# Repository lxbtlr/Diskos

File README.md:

# Diskos
Working directory for all Project Diskos materials

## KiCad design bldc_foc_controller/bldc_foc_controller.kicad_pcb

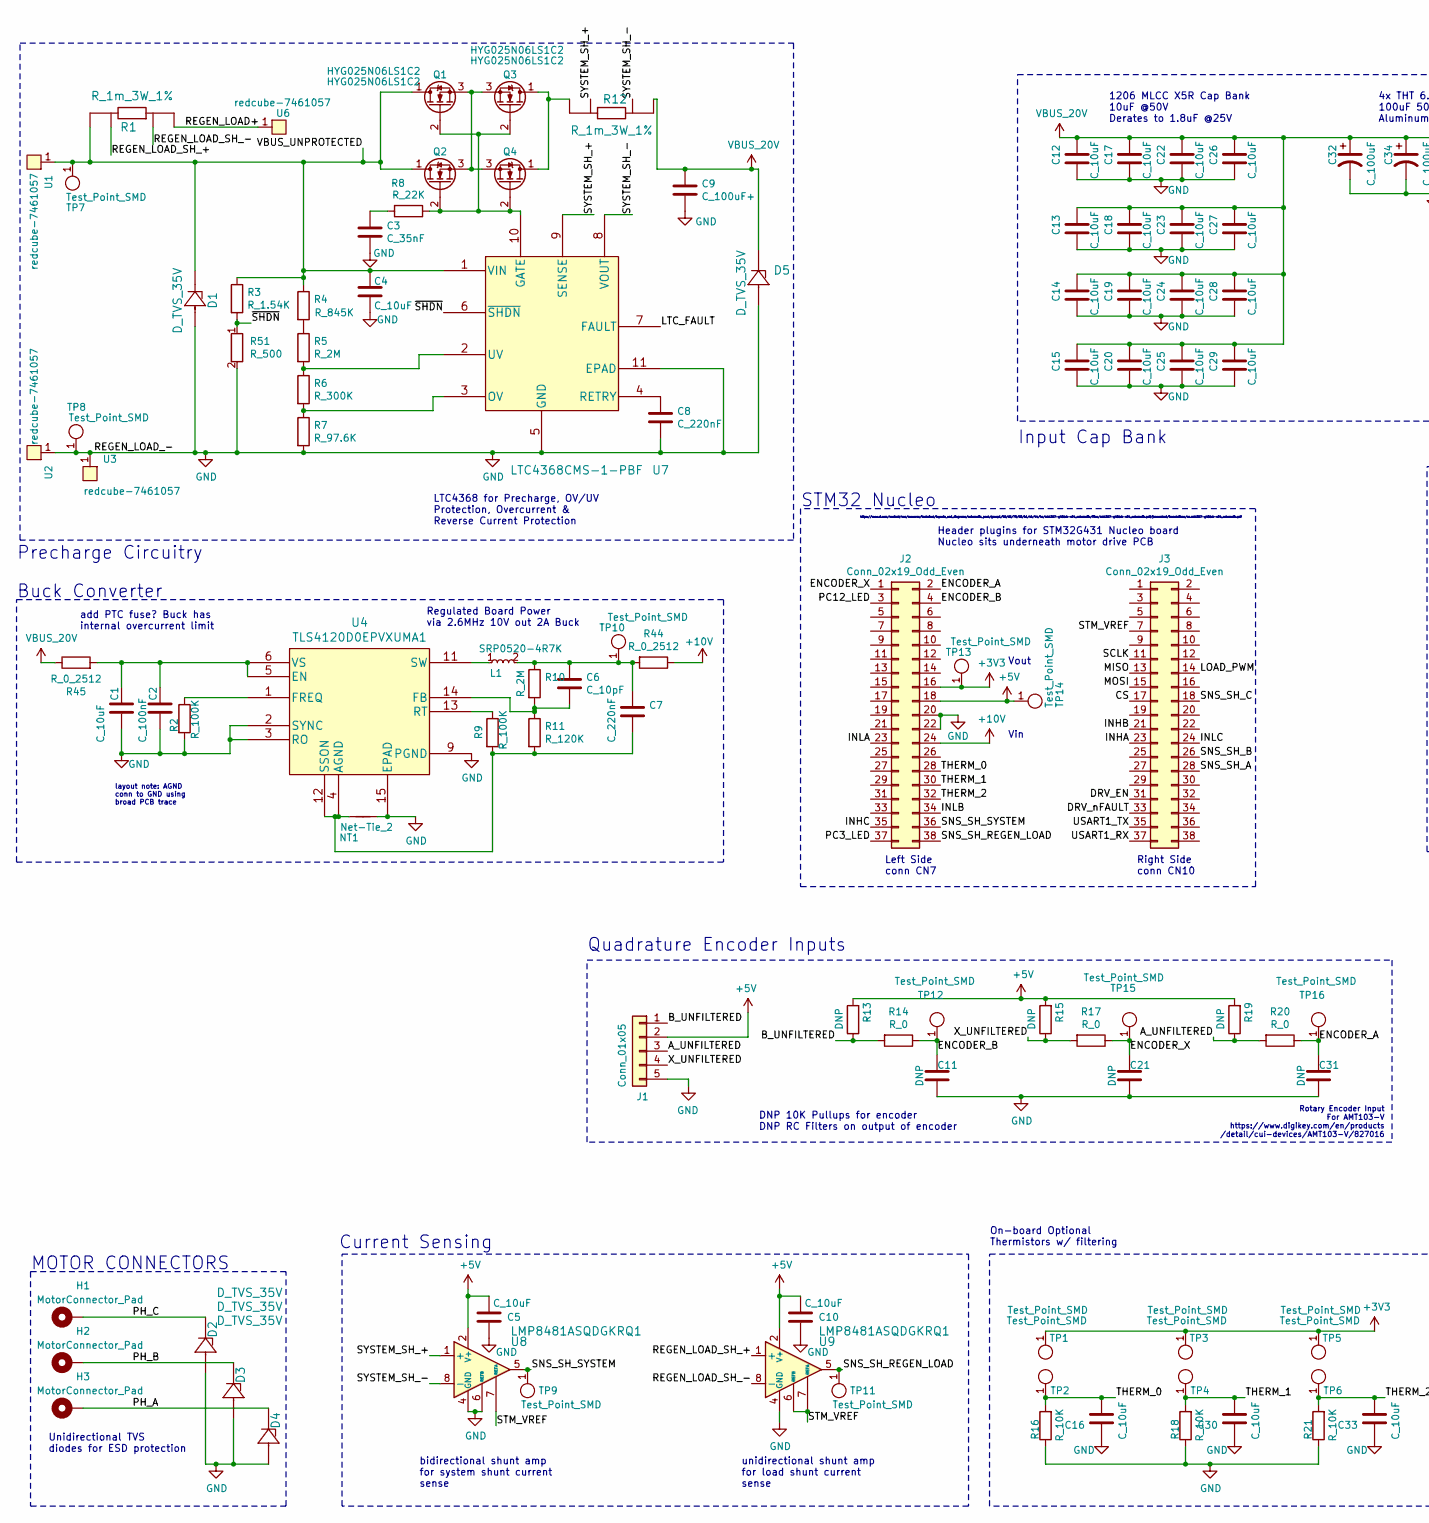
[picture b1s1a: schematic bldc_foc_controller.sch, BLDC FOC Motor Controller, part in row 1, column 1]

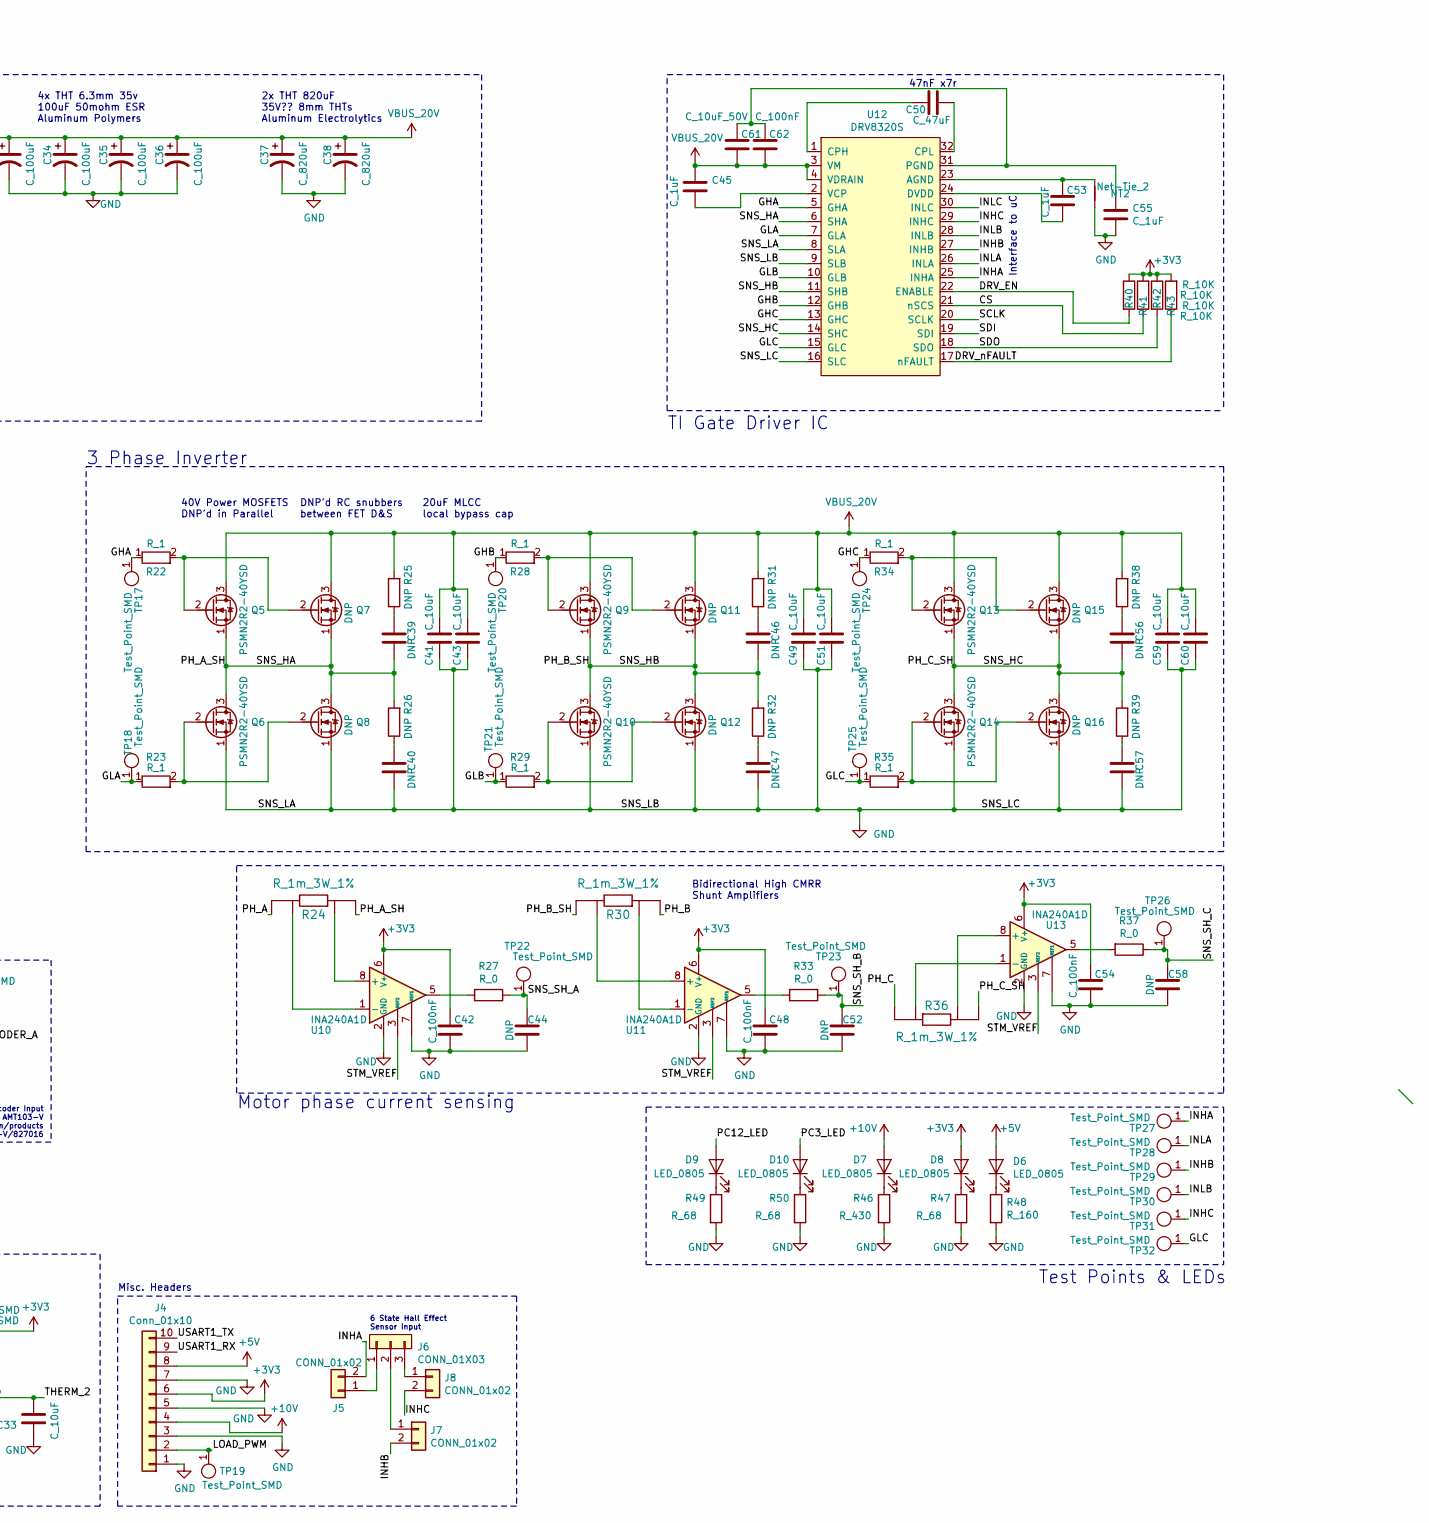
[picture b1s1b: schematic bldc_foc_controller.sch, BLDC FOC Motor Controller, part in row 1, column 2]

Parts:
C1, C4, C5, C10, C16, C30, C33: C_10uF; C_0805_OEM; MPN 1276-1052-1-ND
C2: C_100nF; C_0603_1608Metric; MPN 1276-6717-1-ND
C3: C_35nF; C_0805_OEM
C6: C_10pF; C_0805_OEM
C7, C8: C_220nF; C_0805_OEM
C9: C_100uF+; C_0805_OEM
C11, C21, C31, C39, C40, C44, C46, C47, C52, C56, C57, C58: DNP; C_0805_OEM
C12, C13, C14, C15, C17, C18, C19, C20, C22, C23, C24, C25, C26, C27, C28, C29, C41, C43, C49, C51, C59, C60: C_10uF; C_1206_OEM
C32, C34, C35, C36: C_100uF; CP_Radial_D6.3mm_P2.50mm
C37, C38: C_820uF; CP_Radial_D8.0mm_P3.80mm
C42, C48, C54: C_100nF; C_0805_OEM; MPN 478-3352-1-ND
C45, C53, C55: C_1uF; C_0805_OEM
C50: C_47uF; C_0805_OEM; MPN 1276-6467-1-ND
C61: C_10uF_50V; C_0805_OEM; MPN GRM21BR61H106KE43L
C62: C_100nF; C_0805_OEM; MPN 1276-6717-1-ND
D1, D2, D3, D4, D5: D_TVS_35V; DO-214AB; MPN SMCJ22A-13-F
D6, D7, D8, D9, D10: LED_0805; LED_0805_OEM; MPN 475-1410-1-ND
H1, H2, H3: MotorConnector_Pad; TestPoint_Pad_4.0x4.0mm
J1: Conn_01x05; PinHeader_1x05_P2.54mm_Vertical
J2, J3: Conn_02x19_Odd_Even; PinSocket_2x19_P2.54mm_Vertical
J4: Conn_01x10; PinHeader_1x10_P2.54mm_Vertical
J5, J7, J8: CONN_01x02; PinHeader_1x02_P2.54mm_Vertical; MPN 732-5315-ND
J6: CONN_01X03; PinHeader_1x03_P2.54mm_Vertical_SMD_Pin1Left; MPN 855-M20-9990346
L1: SRP0520-4R7K
NT1, NT2: Net-Tie_2; NetTie-2_SMD_Pad0.5mm
Q1, Q2, Q3, Q4: HYG025N06LS1C2; PDFN_5X6MC_MCH
Q5, Q6, Q9, Q10, Q13, Q14: PSMN2R2-40YSD; LFPAK56
Q7, Q8, Q11, Q12, Q15, Q16: DNP; LFPAK56
R1, R12, R24, R30, R36: R_1m_3W_1%; WSL27261L000FEB; MPN WSL27261L000FEB
R2, R9: R_100K; R_0805_OEM; MPN P100KCCT-ND
R3: R_1.54K; R_0805_OEM; MPN ERJ-6ENF1541V
R4: R_845K; R_0805_OEM
R5, R10: R_2M; R_0805_OEM
R6: R_300K; R_0805_OEM; MPN P300KDACT-ND
R7: R_97.6K; R_0805_OEM
R8: R_22K; R_0805_OEM; MPN RMCF0805JT22K0CT-ND
R11: R_120K; R_0805_OEM; MPN RMCF0805FT120KCT-ND
R13, R15, R19, R25, R26, R31, R32, R38, R39: DNP; R_0805_OEM
R14, R17, R20, R27, R33, R37: R_0; R_0805_OEM
R16, R18, R21, R40, R41, R42, R43: R_10K; R_0805_OEM; MPN CRS0805-FX-1002ELFCT-ND
R22, R23, R28, R29, R34, R35: R_1; R_0805_OEM
R44, R45: R_0_2512; R_2512_OEM; MPN A121322CT-ND
R46: R_430; R_0805_OEM
R47, R49, R50: R_68; R_0805_OEM
R48: R_160; R_0805_OEM
R51: R_500; R_0805_OEM
TP1, TP2, TP3, TP4, TP5, TP6, TP7, TP8, TP10, TP13, TP14, TP19: Test_Point_SMD
TP9, TP11, TP12, TP15, TP16, TP17, TP18, TP20, TP21, TP22, TP23, TP24, TP25, TP26, TP27, TP28, TP29, TP30, TP31, TP32: Test_Point_SMD; TestPoint_Pad_D1.5mm
U1, U2, U3, U6: redcube-7461057; redcube_pressfit_6pin; MPN 7461057
U4: TLS4120D0EPVXUMA1
U7: LTC4368CMS-1-PBF; LTC4368CMS-2-PBF
U8, U9: LMP8481ASQDGKRQ1
U10, U11, U13: INA240A1D; SOIC-8_3.9x4.9mm_P1.27mm
U12: DRV8320S; QFN50P500X500X80-33N

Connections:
+3V3: C42.1, C48.1, C54.1, D8.2 (A), J2.16, J4.6, R40.1, R41.2, R42.1, R43.2, TP1.1, TP3.1, TP5.1, TP13.1, U10.6 (V+), U11.6 (V+), U13.6 (V+)
+5V: C5.1, C10.1, D6.2 (A), J1.2, J2.18, J4.8, R13.2, R15.2, R19.2, TP14.1, U8.2 (V+), U9.2 (V+)
+10V: D7.2 (A), J2.24, J4.4, R44.1
/A_UNFILTERED: J1.3, R19.1, R20.2
/B_UNFILTERED: J1.1, R13.1, R14.2
/CS: J3.17, R41.1, U12.21 (nSCS)
/DRV_EN: J3.31, R40.2, U12.22 (ENABLE)
/DRV_nFAULT: J3.33, R43.1, U12.17 (nFAULT)
/ENCODER_A: C31.1, J2.2, R20.1, TP16.1
/ENCODER_B: C11.1, J2.4, R14.1, TP12.1
/ENCODER_X: C21.1, J2.1, R17.1, TP15.1
/GHA: R22.1, TP17.1, U12.5 (GHA)
/GHB: R28.1, TP20.1, U12.12 (GHB)
/GHC: R34.1, TP24.1, U12.13 (GHC)
/GLA: R23.1, TP18.1, U12.7 (GLA)
/GLB: R29.1, TP21.1, U12.10 (GLB)
/GLC: R35.1, TP25.1, TP32.1, U12.15 (GLC)
/INHA: J3.23, J5.2, TP27.1, U12.25 (INHA)
/INHB: J3.21, J7.2, TP29.1, U12.27 (INHB)
/INHC: J2.35, J8.2, TP31.1, U12.29 (INHC)
/INLA: J2.23, TP28.1, U12.26 (INLA)
/INLB: J2.34, TP30.1, U12.28 (INLB)
/INLC: J3.24, U12.30 (INLC)
/LOAD_PWM: J3.14, J4.2, TP19.1
/LTC_FAULT: U7.7 (FAULT)
/MISO: J3.13
/MOSI: J3.15
/PC3_LED: D10.2 (A), J2.37
/PC12_LED: D9.2 (A), J2.3
/PH_A: D4.1, H3.1, R24.1
/PH_A_SH: C39.2, Q5.1 (S), Q6.3 (D), Q7.1 (S), Q8.3 (D), R24.4, R26.2, U12.6 (SHA)
/PH_B: D3.1, H2.1, R30.4
/PH_B_SH: C46.2, Q9.1 (S), Q10.3 (D), Q11.1 (S), Q12.3 (D), R30.1, R32.2, U12.11 (SHB)
/PH_C: D2.1, H1.1, R36.4
/PH_C_SH: C56.2, Q13.1 (S), Q14.3 (D), Q15.1 (S), Q16.3 (D), R36.1, R39.2, U12.14 (SHC)
/REGEN_LOAD+: R1.4, U6.1
/REGEN_LOAD_SH_+: R1.2, U9.1 (+)
/REGEN_LOAD_SH_-: R1.3, U9.8 (-)
/SCLK: J3.11, U12.20 (SCLK)
/SDI: U12.19 (SDI)
/SDO: R42.2, U12.18 (SDO)
/SNS_SH_A: C44.1, J3.28, R27.1, TP22.1
/SNS_SH_B: C52.1, J3.26, R33.1, TP23.1
/SNS_SH_C: C58.1, J3.18, R37.1, TP26.1
/SNS_SH_REGEN_LOAD: J2.38, TP11.1, U9.5
/SNS_SH_SYSTEM: J2.36, TP9.1, U8.5
/STM_VREF: J3.7, U8.7 (REFA), U9.6 (REFB), U9.7 (REFA), U10.3 (REF2), U11.3 (REF2), U13.3 (REF2)
/SYSTEM_SH_+: R12.3, U7.9 (SENSE), U8.1 (+)
/SYSTEM_SH_-: R12.2, U7.8 (VOUT), U8.8 (-)
/THERM_0: C16.2, J2.28, R16.2, TP2.1
/THERM_1: C30.2, J2.30, R18.2, TP4.1
/THERM_2: C33.2, J2.32, R21.2, TP6.1
/USART1_RX: J3.37, J4.9
/USART1_TX: J3.35, J4.10
/VBUS_UNPROTECTED: C4.1, D1.1, Q1.1 (D), Q2.1 (D), R1.1, R3.1, R4.1, TP7.1, U1.1, U7.1 (VIN)
/X_UNFILTERED: J1.4, R15.1, R17.2
/~SHDN: R3.2, R51.1, U7.6 (~SHDN)
GND: C1.2, C2.2, C3.2, C4.2, C5.2, C8.2, C9.2, C10.2, C11.2, C12.2, C13.2, C14.2, C15.2, C16.1, C17.2, C18.2, C19.2, C20.2, C21.2, C22.2, C23.2, C24.2, C25.2, C26.2, C27.2, C28.2, C29.2, C30.1, C31.2, C32.2, C33.1, C34.2, C35.2, C36.2, C37.2, C38.2, C40.2, C41.2, C42.2, C43.2, C44.2, C47.2, C48.2, C49.2, C51.2, C52.2, C54.2, C55.2, C57.2, C58.2, C59.2, C60.2, D1.2, D2.2, D3.2, D4.2, D5.2, J1.5, J2.20, J2.22, J4.1, J4.3, J4.5, J4.7, NT1.1, NT2.2, Q6.1 (S), Q8.1 (S), Q10.1 (S), Q12.1 (S), Q14.1 (S), Q16.1 (S), R2.2, R7.2, R16.1, R18.1, R21.1, R46.2, R47.2, R48.2, R49.2, R50.2, R51.2, TP8.1, U2.1, U3.1, U4.2 (SYNC), U4.3 (RO), U4.8 (PGND), U4.9 (PGND), U4.15 (EPAD), U7.5 (GND), U7.11 (EPAD), U8.3 (NC), U8.4 (GND), U8.6 (REFB), U9.3 (NC), U9.4 (GND), U10.2 (GND), U10.4 (GND), U10.7 (REF1), U11.2 (GND), U11.4 (GND), U11.7 (REF1), U12.8 (SLA), U12.9 (SLB), U12.16 (SLC), U13.2 (GND), U13.4 (GND), U13.7 (REF1)
unnamed: C3.1, R8.2
unnamed: C6.1, C7.1, L1.2, R10.1, R44.2, TP10.1
unnamed: C6.2, R10.2, R11.1, U4.14 (FB)
unnamed: C7.2, NT1.2, R9.2, R11.2, U4.4 (AGND), U4.12 (SSON)
unnamed: C8.1, U7.4 (RETRY)
unnamed: C39.1, R25.1
unnamed: C40.1, R26.1
unnamed: C45.2, U12.2 (VCP)
unnamed: C46.1, R31.1
unnamed: C47.1, R32.1
unnamed: C50.1, U12.32 (CPL)
unnamed: C50.2, U12.1 (CPH)
unnamed: C53.1, NT2.1, U12.23 (AGND)
unnamed: C53.2, U12.24 (DVDD)
unnamed: C55.1, C61.1, C62.1, U12.31 (PGND)
unnamed: C56.1, R38.1
unnamed: C57.1, R39.1
unnamed: D6.1 (K), R48.1
unnamed: D7.1 (K), R46.1
unnamed: D8.1 (K), R47.1
unnamed: D9.1 (K), R49.1
unnamed: D10.1 (K), R50.1
unnamed: J5.1, J6.1
unnamed: J6.2, J7.1
unnamed: J6.3, J8.1
unnamed: L1.1, U4.10 (SW), U4.11 (SW)
unnamed: Q1.2 (G), Q2.2 (G), Q3.2 (G), Q4.2 (G), R8.1, U7.10 (GATE)
unnamed: Q1.3 (S), Q2.3 (S), Q3.3 (S), Q4.3 (S)
unnamed: Q3.1 (D), Q4.1 (D), R12.4
unnamed: Q5.2 (G), Q7.2 (G), R22.2
unnamed: Q6.2 (G), Q8.2 (G), R23.2
unnamed: Q10.2 (G), Q12.2 (G), R29.2
unnamed: Q9.2 (G), Q11.2 (G), R28.2
unnamed: Q13.2 (G), Q15.2 (G), R34.2
unnamed: Q14.2 (G), Q16.2 (G), R35.2
unnamed: R2.1, U4.1 (FREQ)
unnamed: R4.2, R5.1
unnamed: R5.2, R6.1, U7.2 (UV)
unnamed: R6.2, R7.1, U7.3 (OV)
unnamed: R9.1, U4.13 (RT)
unnamed: R24.2, U10.1 (-)
unnamed: R24.3, U10.8 (+)
unnamed: R27.2, U10.5
unnamed: R30.2, U11.8 (+)
unnamed: R30.3, U11.1 (-)
unnamed: R33.2, U11.5
unnamed: R36.2, U13.8 (+)
unnamed: R36.3, U13.1 (-)
unnamed: R37.2, U13.5
VBUS: C9.1, C12.1, C13.1, C14.1, C15.1, C17.1, C18.1, C19.1, C20.1, C22.1, C23.1, C24.1, C25.1, C26.1, C27.1, C28.1, C29.1, C32.1, C34.1, C35.1, C36.1, C37.1, C38.1, C41.1, C43.1, C45.1, C49.1, C51.1, C59.1, C60.1, C61.2, C62.2, D5.1, Q5.3 (D), Q7.3 (D), Q9.3 (D), Q11.3 (D), Q13.3 (D), Q15.3 (D), R12.1, R25.2, R31.2, R38.2, R45.1, U12.3 (VM), U12.4 (VDRAIN)
VS: C1.1, C2.1, R45.2, U4.5 (EN), U4.6 (VS), U4.7 (VS)

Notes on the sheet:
Left Side conn CN7
Right Side conn CN10
3 Phase Inverter
https://www.st.com/content/ccc/resource/technical/layouts_and_diagrams/schematic_pack/group1/98/d2/70/60/b1/cb/44/4c/mb1367-g431rb-c04_schematic/files/mb1367-g431rb-c04_schematic.pdf/jcr:content/translations/en.mb1367-g431rb-c04_schematic.pdf
Rotary Encoder Input For AMT103-V https://www.digikey.com/en/products /detail/cui-devices/AMT103-V/827016
6 State Hall Effect Sensor Input
Regulated Board Power via 2.6MHz 10V out 2A Buck
Vin
Vout
On-board Optional Thermistors w/ filtering
add PTC fuse? Buck has internal overcurrent limit
layout note: AGND conn to GND using broad PCB trace
TI Gate Driver IC
LTC4368 for Precharge, OV/UV Protection, Overcurrent & Reverse Current Protection
4x THT 6.3mm 35v 100uF 50mohm ESR Aluminum Polymers
2x THT 820uF 35V?? 8mm THTs Aluminum Electrolytics
Input Cap Bank
40V Power MOSFETS DNP'd in Parallel
bidirectional shunt amp for system shunt current sense
DNP'd RC snubbers between FET D&S
20uF MLCC local bypass cap
DNP 10K Pullups for encoder DNP RC Filters on output of encoder
Quadrature Encoder Inputs
47nF x7r
Interface to uC
unidirectional shunt amp for load shunt current sense
MOTOR CONNECTORS
Unidirectional TVS diodes for ESD protection
Current Sensing
Precharge Circuitry
Buck Converter
STM32 Nucleo
Misc. Headers
Motor phase current sensing
1206 MLCC X5R Cap Bank 10uF @50V Derates to 1.8uF @25V
Test Points & LEDs
Header plugins for STM32G431 Nucleo board Nucleo sits underneath motor drive PCB
Bidirectional High CMRR Shunt Amplifiers

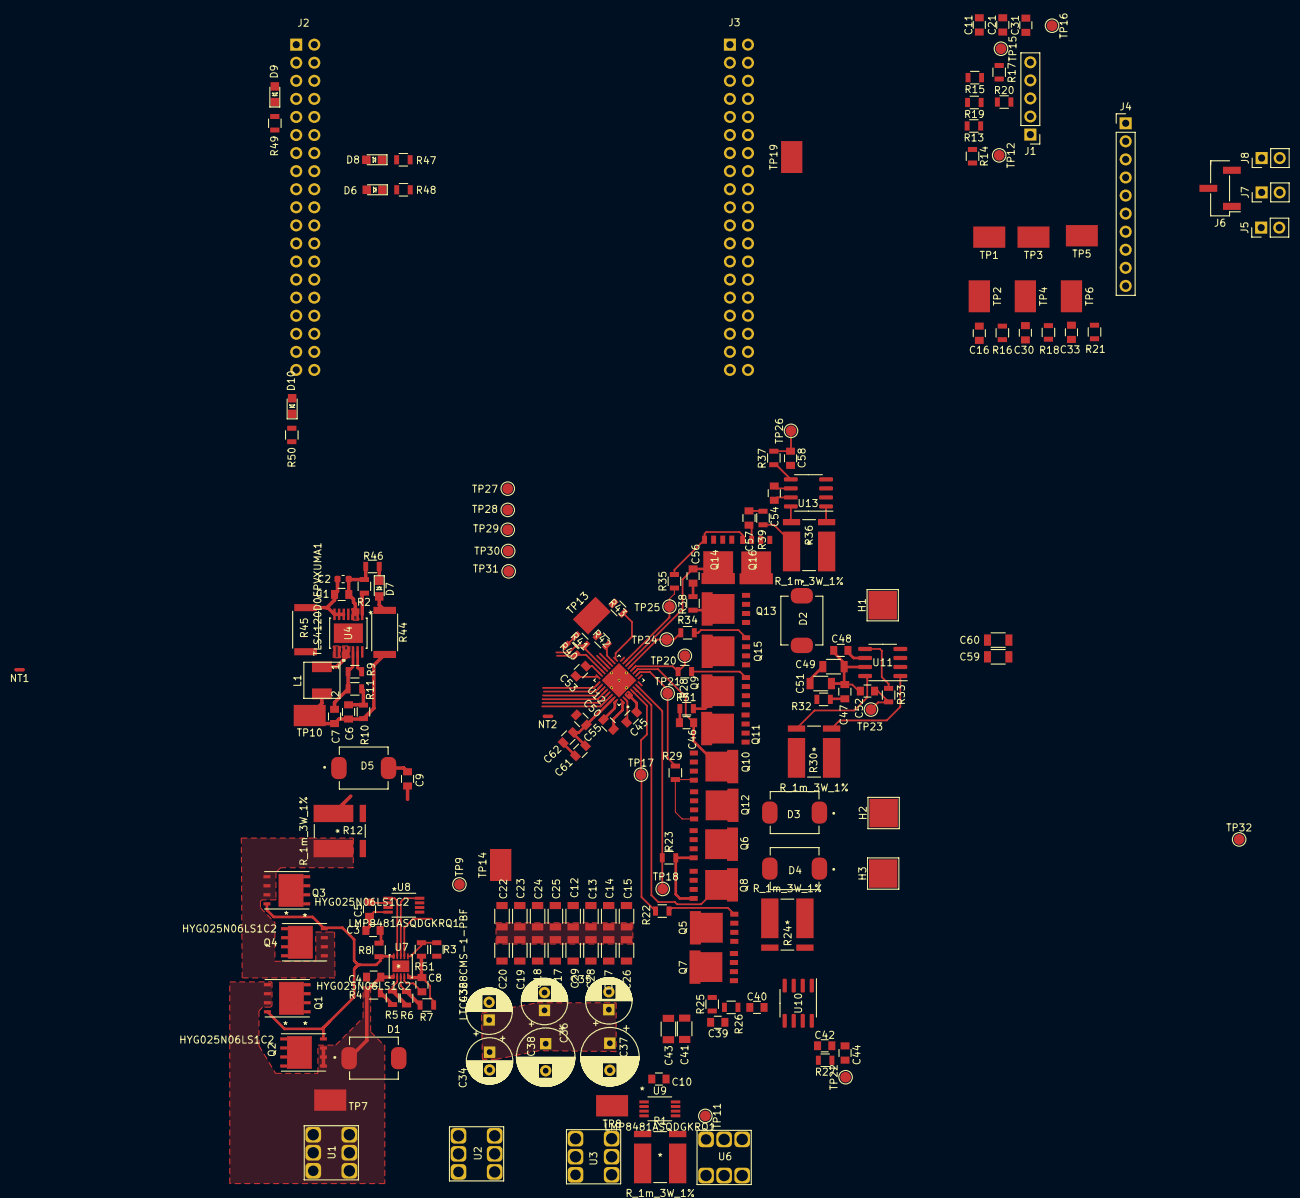
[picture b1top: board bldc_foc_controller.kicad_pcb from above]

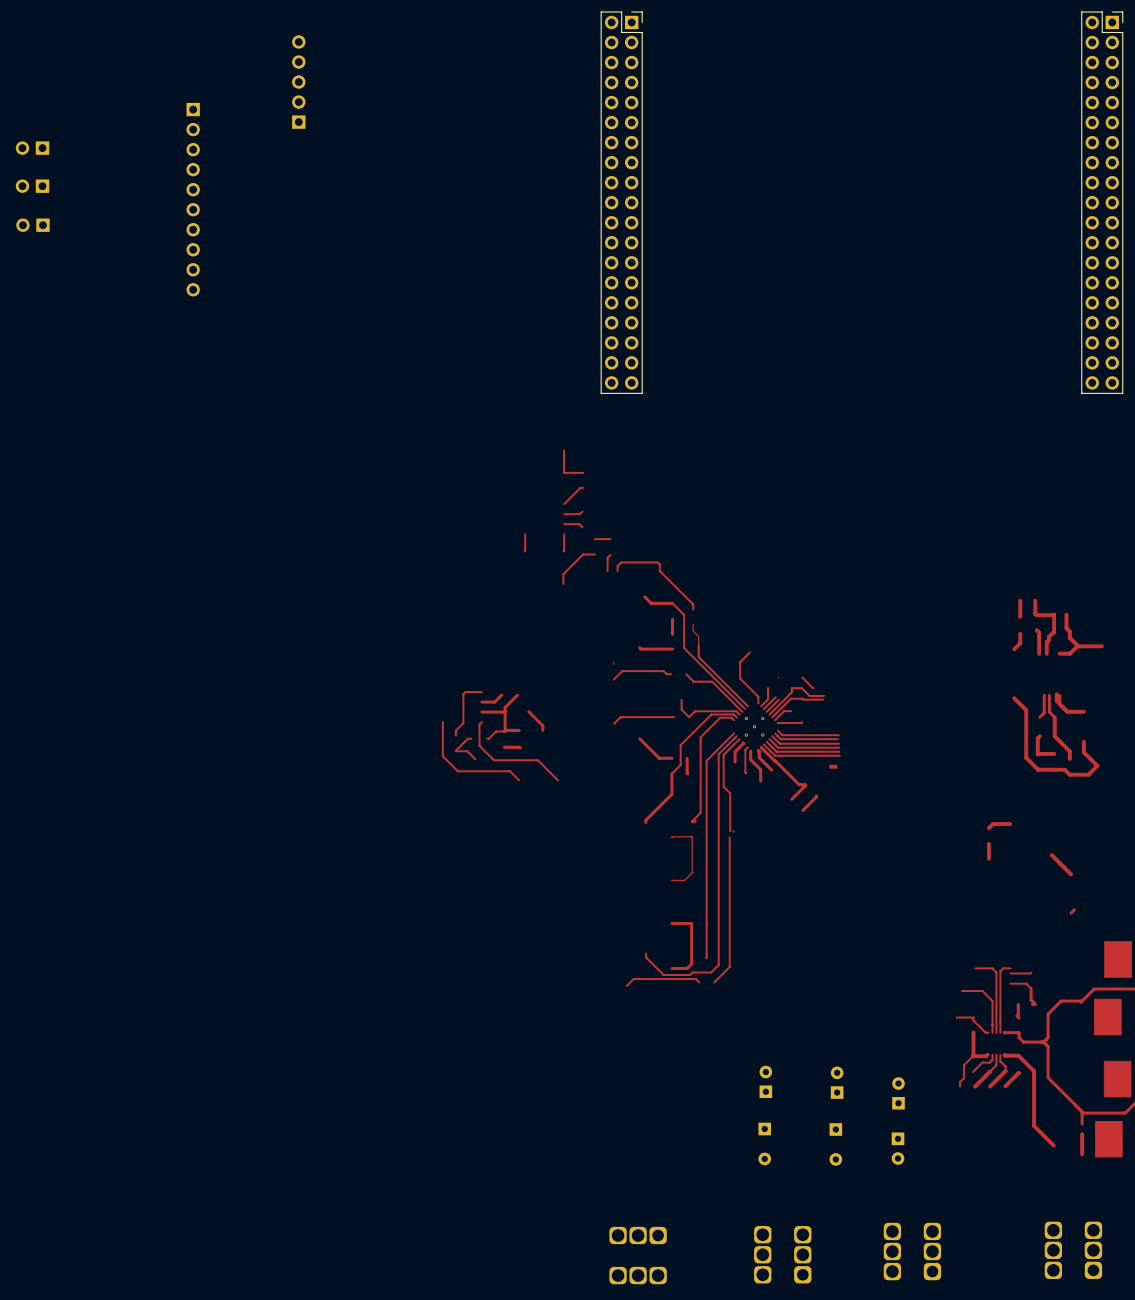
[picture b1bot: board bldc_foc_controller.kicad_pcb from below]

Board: 4 copper layers, 197 parts (2 on the bottom side), 105 nets.

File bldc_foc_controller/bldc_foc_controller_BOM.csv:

Reference, Quantity, Value, Footprint, Datasheet, MPN, MFN, PurchasingLink, Desc, Link, Purchasing Link
C1 C4 C5 C10 C16 C30 C33 ,7,"C_10uF","footprints:C_0805_OEM","http://www.samsungsem.com/kr/support/product-search/mlcc/__i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","1276-1052-1-ND","DK","https://www.digikey.com/product-detail/en/samsung-electro-me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","","",""
C12 C13 C14 C15 C17 C18 C19 C20 C22 C23 C24 C25 C26 C27 C28 C29 C41 C43 C49 C51 C59 C60 ,22,"C_10uF","footprints:C_1206_OEM","https://media.digikey.com/pdf/Data%20Sheets/Samsung%20PDFs/C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"
C2 ,1,"C_100nF","footprints:C_0603_1608Metric","http://www.samsungsem.com/kr/support/product-search/mlcc/CL1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","1276-6717-1-ND","DK","https://www.digikey.com/product-detail/en/samsung-electro-me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","","",""
C3 ,1,"C_35nF","footprints:C_0805_OEM","~"
C32 C34 C35 C36 ,4,"C_100uF","Capacitor_THT:CP_Radial_D6.3mm_P2.50mm","","","","","THT 6.3mm 35v 100uF 50mohm alpolys for 15c each","",""
C37 C38 ,2,"C_820uF","Capacitor_THT:CP_Radial_D8.0mm_P3.80mm","","","","","820uF 8mm Alelec THTs for 21c","",""
C11 C21 C31 C39 C40 C44 C46 C47 C52 C56 C57 C58 ,12,"DNP","footprints:C_0805_OEM","~"
C50 ,1,"C_47uF","footprints:C_0805_OEM","http://www.samsungsem.com/kr/support/product-search/mlcc/__i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","1276-6467-1-ND","DK","https://www.digikey.com/product-detail/en/samsung-electro-me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","","",""
C45 C53 C55 ,3,"C_1uF","footprints:C_0805_OEM","https://www.yageo.com/upload/media/product/productsearch/dat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","","","https://www.digikey.com/product-detail/en/yageo/CC0805ZKY5V9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","","",""
C42 C48 C54 C62 ,4,"C_100nF","footprints:C_0805_OEM","http://datasheets.avx.com/X7RDielectric.pdf","478-3352-1-ND","DK","https://www.digikey.com/products/en?keywords=478-3352-1-ND","","",""
C6 ,1,"C_10pF","footprints:C_0805_OEM","~"
C61 ,1,"C_10uF_50V","footprints:C_0805_OEM","http://www.samsungsem.com/kr/support/product-https://search.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","GRM21BR61H106KE43L","Murata","https://www.digikey.com/en/products/detail/murata-electronic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","","",""
C7 C8 ,2,"C_220nF","footprints:C_0805_OEM","https://www.yageo.com/upload/media/product/productsearch/dat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","","","https://www.digikey.com/product-detail/en/yageo/CC0805ZRY5V9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","","",""
C9 ,1,"C_100uF+","footprints:C_0805_OEM","https://www.nichicon.co.jp/english/products/pdfs/e-uuq.pdf","","","https://www.digikey.com/product-detail/en/nichicon/UUQ1H101M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","","",""
D1 D2 D3 D4 D5 ,5,"D_TVS_35V","footprints:DO-214AB","https://www.diodes.com/assets/Datasheets/ds40741.pdf","SMCJ22A-13-F","","","","",""
D6 D7 D8 D9 D10 ,5,"LED_0805","footprints:LED_0805_OEM","http://www.osram-os.com/Graphics/XPic9/00078860_0.pdf","475-1410-1-ND","DK","https://www.digikey.com/products/en?keywords=475-1410-1-ND","","",""
H1 H2 H3 ,3,"MotorConnector_Pad","TestPoint:TestPoint_Pad_4.0x4.0mm","~"
J1 ,1,"Conn_01x05","Connector_PinHeader_2.54mm:PinHeader_1x05_P2.54mm_Vertical","~"
J2 J3 ,2,"Conn_02x19_Odd_Even","Connector_PinSocket_2.54mm:PinSocket_2x19_P2.54mm_Vertical","~"
J4 ,1,"Conn_01x10","footprints:PinHeader_1x10_P2.54mm_Vertical",""
J6 ,1,"CONN_01X03","Connector_PinHeader_2.54mm:PinHeader_1x03_P2.54mm_Vertical_SMD_Pin1Left","https://www.mouser.com/datasheet/2/181/M20-999-1218971.pdf","855-M20-9990346","Mouser","https://www.mouser.com/ProductDetail/Harwin/M20-9990346?qs=s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","","",""
J5 J7 J8 ,3,"CONN_01x02","footprints:PinHeader_1x02_P2.54mm_Vertical","https://katalog.we-online.de/em/datasheet/6130xx11121.pdf","732-5315-ND","DK","","","",""
L1 ,1,"SRP0520-4R7K","footprints:SRP0520-4R7K","https://www.bourns.com/docs/product-datasheets/srp0520.pdf"
NT1 NT2 ,2,"Net-Tie_2","NetTie:NetTie-2_SMD_Pad0.5mm","~"
Q1 Q2 Q3 Q4 ,4,"HYG025N06LS1C2","footprints:PDFN_5X6MC_MCH","https://drive.google.com/file/d/1Gbielo2qQ6OtCDVvoQN8r_uS-8E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"
Q5 Q6 Q9 Q10 Q13 Q14 ,6,"PSMN2R2-40YSD","footprints:LFPAK56","https://assets.nexperia.com/documents/data-sheet/PSMN2R2-40YSD.pdf"
Q7 Q8 Q11 Q12 Q15 Q16 ,6,"DNP","footprints:LFPAK56","https://assets.nexperia.com/documents/data-sheet/PSMN2R2-40YSD.pdf"
R1 R36 ,2,"R_1m_3W_1%","footprints:WSL27261L000FEB","https://www.vishay.com/docs/30131/wsl2726.pdf","WSL27261L000FEB","","","","",""
R5 R10 ,2,"R_2M","footprints:R_0805_OEM","~"
R11 ,1,"R_120K","footprints:R_0805_OEM","https://www.seielect.com/Catalog/SEI-RMCF_RMCP.pdf","RMCF0805FT120KCT-ND","DK","https://www.digikey.com/product-detail/en/stackpole-electron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","","",""
R14 R17 R20 R27 R33 R37 ,6,"R_0","footprints:R_0805_OEM","~"
R2 R9 ,2,"R_100K","footprints:R_0805_OEM","https://industrial.panasonic.com/cdbs/www-data/pdf/RDA0000/A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","P100KCCT-ND","DK","https://www.digikey.com/product-detail/en/panasonic-electron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","","",""
R16 R18 R21 R40 R41 R42 R43 ,7,"R_10K","footprints:R_0805_OEM","http://www.bourns.com/data/global/pdfs/CRS.pdf","CRS0805-FX-1002ELFCT-ND","DK","https://www.digikey.com/products/en?keywords=CRS0805-FX-1002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","","",""
R22 R23 R28 R29 R34 R35 ,6,"R_1","footprints:R_0805_OEM","","","","","","https://www.digikey.com/product-detail/en/yageo/RC0603FR-071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",""
R12 R24 R30 ,3,"R_1m_3W_1%","formula:WSL27261L000FEB","https://www.vishay.com/docs/30131/wsl2726.pdf","WSL27261L000FEB","","","","",""
R13 R15 R19 R25 R26 R31 R32 R38 R39 ,9,"DNP","footprints:R_0805_OEM","~"
R3 ,1,"R_1.54K","footprints:R_0805_OEM","https://industrial.panasonic.com/cdbs/www-data/pdf/RDA0000/A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","ERJ-6ENF1541V","Panasonic","","","","https://www.digikey.com/en/products/detail/panasonic-electro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"
R4 ,1,"R_845K","footprints:R_0805_OEM","https://www.digikey.com/en/products/detail/stackpole-electro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"
R44 R45 ,2,"R_0_2512","footprints:R_2512_OEM","http://www.te.com/commerce/DocumentDelivery/DDEController?Ac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","A121322CT-ND","DK","https://www.digikey.com/products/en?keywords=A121322CT-ND","","",""
R46 ,1,"R_430","footprints:R_0805_OEM","~"
R47 R49 R50 ,3,"R_68","footprints:R_0805_OEM","~"
R48 ,1,"R_160","footprints:R_0805_OEM","~"
R51 ,1,"R_500","footprints:R_0805_OEM",""
R6 ,1,"R_300K","footprints:R_0805_OEM","https://industrial.panasonic.com/cdbs/www-data/pdf/RDM0000/A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","P300KDACT-ND","DK","https://www.digikey.com/product-detail/en/panasonic-electron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","","",""
R7 ,1,"R_97.6K","footprints:R_0805_OEM","~"
R8 ,1,"R_22K","footprints:R_0805_OEM","https://www.seielect.com/Catalog/SEI-RMCF_RMCP.pdf","RMCF0805JT22K0CT-ND","DK","https://www.digikey.com/products/en?keywords=RMCF0805JT22K0CT-ND","","",""
TP9 TP11 TP12 TP15 TP16 TP17 TP18 TP20 TP21 TP22 TP23 TP24 TP25 TP26 TP27 TP28 TP29 TP30 TP31 TP32 ,20,"Test_Point_SMD","TestPoint:TestPoint_Pad_D1.5mm",""
TP1 TP2 TP3 TP4 TP5 TP6 TP7 TP8 TP10 TP13 TP14 TP19 ,12,"Test_Point_SMD","footprints:Test_Point_SMD",""
U12 ,1,"DRV8320S","footprints:QFN50P500X500X80-33N","https://www.ti.com/lit/ds/symlink/drv8320r.pdf?HQS=dis-dk-nu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"
U10 U11 U13 ,3,"INA240A1D","Package_SO:SOIC-8_3.9x4.9mm_P1.27mm","http://www.ti.com/lit/ds/symlink/ina240.pdf"
U4 ,1,"TLS4120D0EPVXUMA1","footprints:TLS4120D0EPVXUMA1","https://www.infineon.com/dgdl/Infineon-TLS4120D0EPV-DataShee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"
U1 U2 U3 U6 ,4,"redcube-7461057","footprints:redcube_pressfit_6pin","https://www.mouser.com/datasheet/2/445/7461057-1723744.pdf","7461057","","","","",""
U7 ,1,"LTC4368CMS-1-PBF","footprints:LTC4368CMS-2-PBF","https://www.analog.com/media/en/technical-documentation/data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"
U8 U9 ,2,"LMP8481ASQDGKRQ1","footprints:LMP8481ASQDGKRQ1","https://www.ti.com/lit/ds/symlink/lmp8480-q1.pdf?HQS=dis-dk-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"

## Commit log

2021-10-30 made kicad template
2021-11-01 rpm measurement code to be tested
2021-11-03 updated v0 code heavily
2021-11-03 oops, added in avery code for testing
2021-11-04 everythign works except rpm measurement
2021-11-07 schem and code
2021-11-14 schematic updates
2021-11-16 schem changes
2021-11-16 schem changes fr
2021-11-16 more schem changes
2021-11-16 more schem chagnes
2021-11-16 simple changes yuh
2021-11-16 minor changes
2021-11-17 layout changes
2021-11-17 changes to schem
2021-11-17 Laying it out
2021-11-17 buck layout set
2021-11-17 fixing merge errors
2021-11-17 additional merge fixes
2021-11-17 more layout, ay
2021-11-17 layout pushing
2021-11-18 schem changes, layout changes
2021-11-27 still finishing inverter and other layouts
2021-11-27 moving comps to the board
2021-11-28 housekeeping
2021-11-28 major layout update
2021-11-28 quick layout push
2021-12-01 updates to arduino code
2021-12-06 establishing basis for website
2021-12-07 messing with odrive & arduino code a lil
2021-12-08 website additions
2021-12-08 roomate push
2021-12-08 wrapping up templates
2021-12-08 more templates finsihed
2021-12-09 state machine in code
2021-12-10 code changes
2021-12-10 updated IMU to include current sensor
2021-12-14 code updates
2021-12-14 repo update
2021-12-14 wiped printlines
2021-12-14 imu works
2021-12-14 broke IMU, serial comms are broke
2021-12-14 stuff works again, blame I2C IMU, need to confirm actual datarate
2021-12-14 arduino code updates
2021-12-14 added serial-studio .json
2021-12-15 added magnetics section + video
2021-12-15 added manufacturing
2021-12-15 added manufacturing - fully yuh
2021-12-15 wrapped mechanical design - website
2021-12-15 more website additions on frontpage
2021-12-15 motorcontroller added to website
2021-12-16 finished most of website
2021-12-16 finished website

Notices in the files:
parts and their libraries:
Copyright 2021 Accelerated Designs. All rights reserved.
